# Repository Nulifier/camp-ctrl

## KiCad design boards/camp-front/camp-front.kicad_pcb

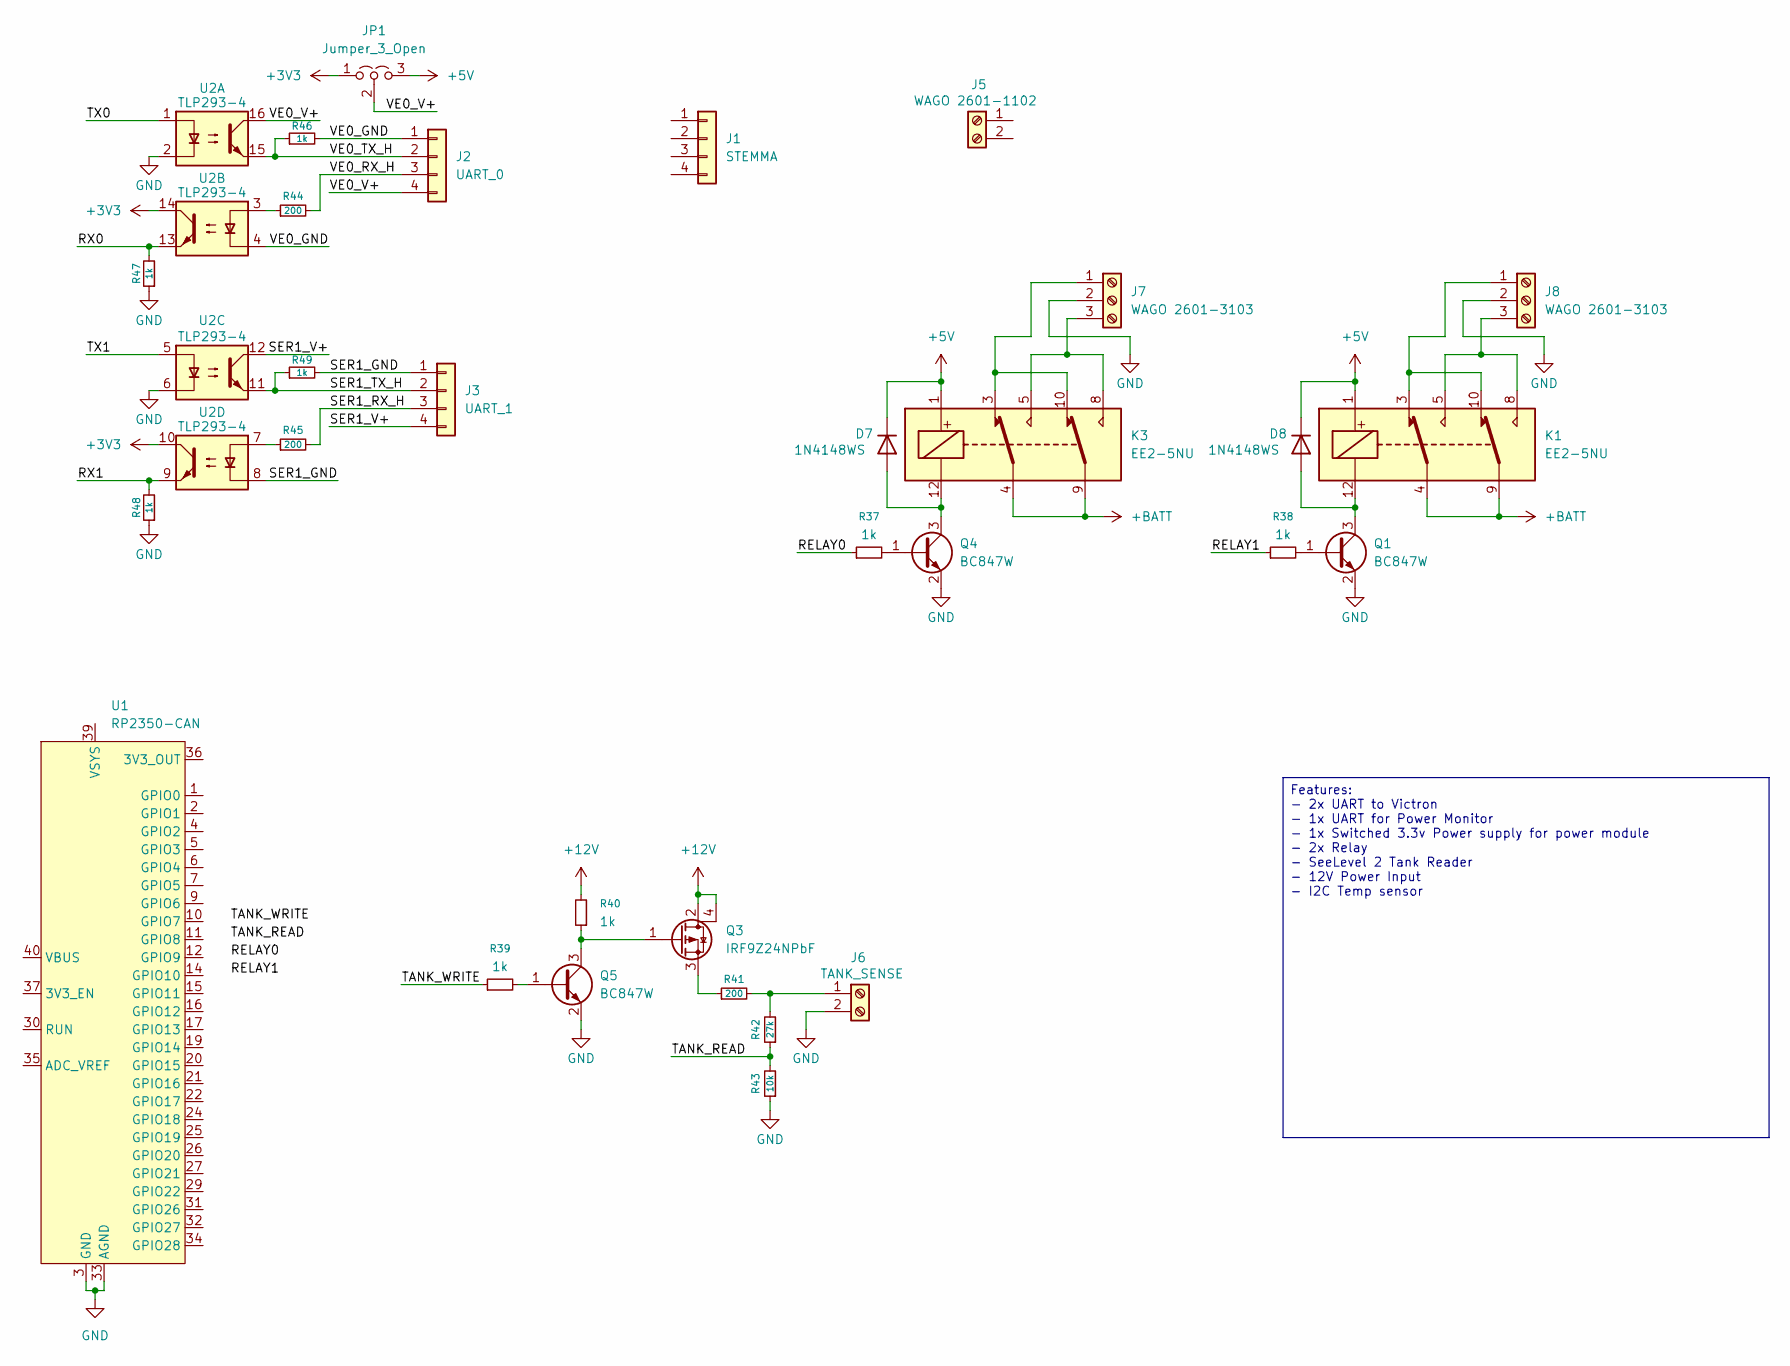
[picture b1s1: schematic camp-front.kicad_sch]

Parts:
D7, D8: 1N4148WS; D_SOD-323
J1: STEMMA; JST_PH_B4B-PH-K_1x04_P2.00mm_Vertical; Digikey 455-B4B-PH-K-ND
J2: UART_0; JST_PH_B4B-PH-K_1x04_P2.00mm_Vertical; Digikey 455-B4B-PH-K-ND
J3: UART_1; JST_PH_B4B-PH-K_1x04_P2.00mm_Vertical; Digikey 455-B4B-PH-K-ND
J5: WAGO 2601-1102; TerminalBlock_WAGO_2601-1102_1x02_P3.50mm_Horizontal; Digikey 2946-2601-1102-ND
J6: TANK_SENSE; TerminalBlock_WAGO_2601-1102_1x02_P3.50mm_Horizontal; Digikey 2946-2601-1102-ND
J7, J8: WAGO 2601-3103; TerminalBlock_WAGO_2601-1103_1x03_P3.50mm_Horizontal; Digikey 2946-2601-1103-ND
JP1: Jumper_3_Open; PinHeader_1x03_P1.00mm_Vertical
K1, K3: EE2-5NU; Relay_DPDT_Kemet_EE2_NU
Q1, Q4, Q5: BC847W; SOT-323_SC-70
Q3: IRF9Z24NPbF; TO-220-3_Horizontal_TabDown
R37, R38, R39, R40, R46, R47, R48, R49: 1k; R_0805_2012Metric_Pad1.20x1.40mm_HandSolder
R41, R44, R45: 200; R_0805_2012Metric_Pad1.20x1.40mm_HandSolder
R42: 27k; R_0805_2012Metric_Pad1.20x1.40mm_HandSolder
R43: 10k; R_0805_2012Metric_Pad1.20x1.40mm_HandSolder
U1: RP2350-CAN
U2: TLP293-4; SOIC-16_4.55x10.3mm_P1.27mm; Digikey TLP293-4(GB-TPECT-ND

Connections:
+3V3: JP1.1 (A), U2.10, U2.14
+5V: D7.1 (K), D8.1 (K), JP1.3 (B), K1.1, K3.1
+12V: Q3.2 (D), Q3.4 (D), R40.2
+BATT: K1.4, K1.9, K3.4, K3.9
/RELAY0: R37.1
/RELAY1: R38.1
/RX0: R47.2, U2.13
/RX1: R48.2, U2.9
/SER1_GND: J3.1, R49.2, U2.8
/SER1_RX_H: J3.3, R45.2
/SER1_TX_H: J3.2, R49.1, U2.11
/SER1_V+: J3.4, U2.12
/TANK_READ: R42.1, R43.2
/TANK_WRITE: R39.1
/TX0: U2.1
/TX1: U2.5
/VE0_GND: J2.1, R46.2, U2.4
/VE0_RX_H: J2.3, R44.2
/VE0_TX_H: J2.2, R46.1, U2.15
/VE0_V+: J2.4, JP1.2 (C), U2.16
GND: J6.2, J7.2, J8.2, Q1.2 (E), Q4.2 (E), Q5.2 (E), R43.1, R47.1, R48.1, U1.3 (GND), U1.8 (GND), U1.13 (GND), U1.18 (GND), U1.23 (GND), U1.28 (GND), U1.33 (AGND), U1.38 (GND), U2.2, U2.6
unnamed: D7.2 (A), K3.12, Q4.3 (C)
unnamed: D8.2 (A), K1.12, Q1.3 (C)
unnamed: J6.1, R41.2, R42.2
unnamed: J7.1, K3.3, K3.10
unnamed: J7.3, K3.5, K3.8
unnamed: J8.1, K1.3, K1.10
unnamed: J8.3, K1.5, K1.8
unnamed: Q1.1 (B), R38.2
unnamed: Q3.1 (G), Q5.3 (C), R40.1
unnamed: Q3.3 (S), R41.1
unnamed: Q4.1 (B), R37.2
unnamed: Q5.1 (B), R39.2
unnamed: R44.1, U2.3
unnamed: R45.1, U2.7

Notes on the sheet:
Features: - 2x UART to Victron - 1x UART for Power Monitor - 1x Switched 3.3v Power supply for power module - 2x Relay - SeeLevel 2 Tank Reader - 12V Power Input - I2C Temp sensor

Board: 2 copper layers, 31 parts (0 on the bottom side), 30 nets, no tracks yet.

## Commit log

2026-03-13 Initial checkin for ve.direct
2026-03-13 Added cargo workspace
2026-03-16 Added docs
2026-03-16 Some cleanup
2026-03-16 Started on the registers
2026-03-17 Added almost all of the register addresses
2026-03-17 Added generic implementation to bitflags
2026-03-17 Added all the text fields
2026-03-20 Added LVGL vendor libs
2026-03-20 Added some text stuff
2026-03-23 Built more of the GUI
2026-03-25 Developed lvgl port
2026-03-25 Added more styles
2026-03-30 Finished adding styles
2026-04-08 Restructuring and started embedded design
2026-04-08 Added datasheet and schematic
2026-04-13 Started working on LVGL integration
2026-04-17 Started developing display driver
2026-04-17 Split the RGB resources from the rest of the display
2026-04-17 Added test pattern
2026-04-17 Added explicit pin mapping
2026-04-17 Changed start order of PIO
2026-04-17 Split the PIO programs out
2026-04-17 Screen displays properly
2026-04-19 Example SeeLevel code
2026-04-20 Started adding fill task
2026-04-24 Got newer design working with pushing chunks but still too slow
2026-04-24 Added front board
2026-04-27 Got the DMA working in the quad DMA ping-pong.
2026-04-27 Got the two DMA approach working
2026-04-29 Got the display working
2026-04-30 Added temperature sensor
2026-04-30 Cleaned up a bit
2026-04-30 Got VSYNC working
2026-05-04 Got the GUI mostly displaying
2026-05-05 Slight mods
2026-05-05 Worked on boards
